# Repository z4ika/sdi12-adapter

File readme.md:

## SDI-12 to USB Type-B Adapter Board PCB
KiCAD project for an adapter powered by a common STM32G431 series microcontroller chip using the on-chip USB capabilities to communicate with a PC relying on VCOM CDC option, to allow for an easy communication.

Current revision includes bidirectional 5V - 3.3V level shifting without logical voltage level inversion. This ensures compability of SDI standard with TTL logic. All of the parts have been standarized and designated manufacturer is JLCPCB. Project includes index.html as BOM listing. 

## 3D renders

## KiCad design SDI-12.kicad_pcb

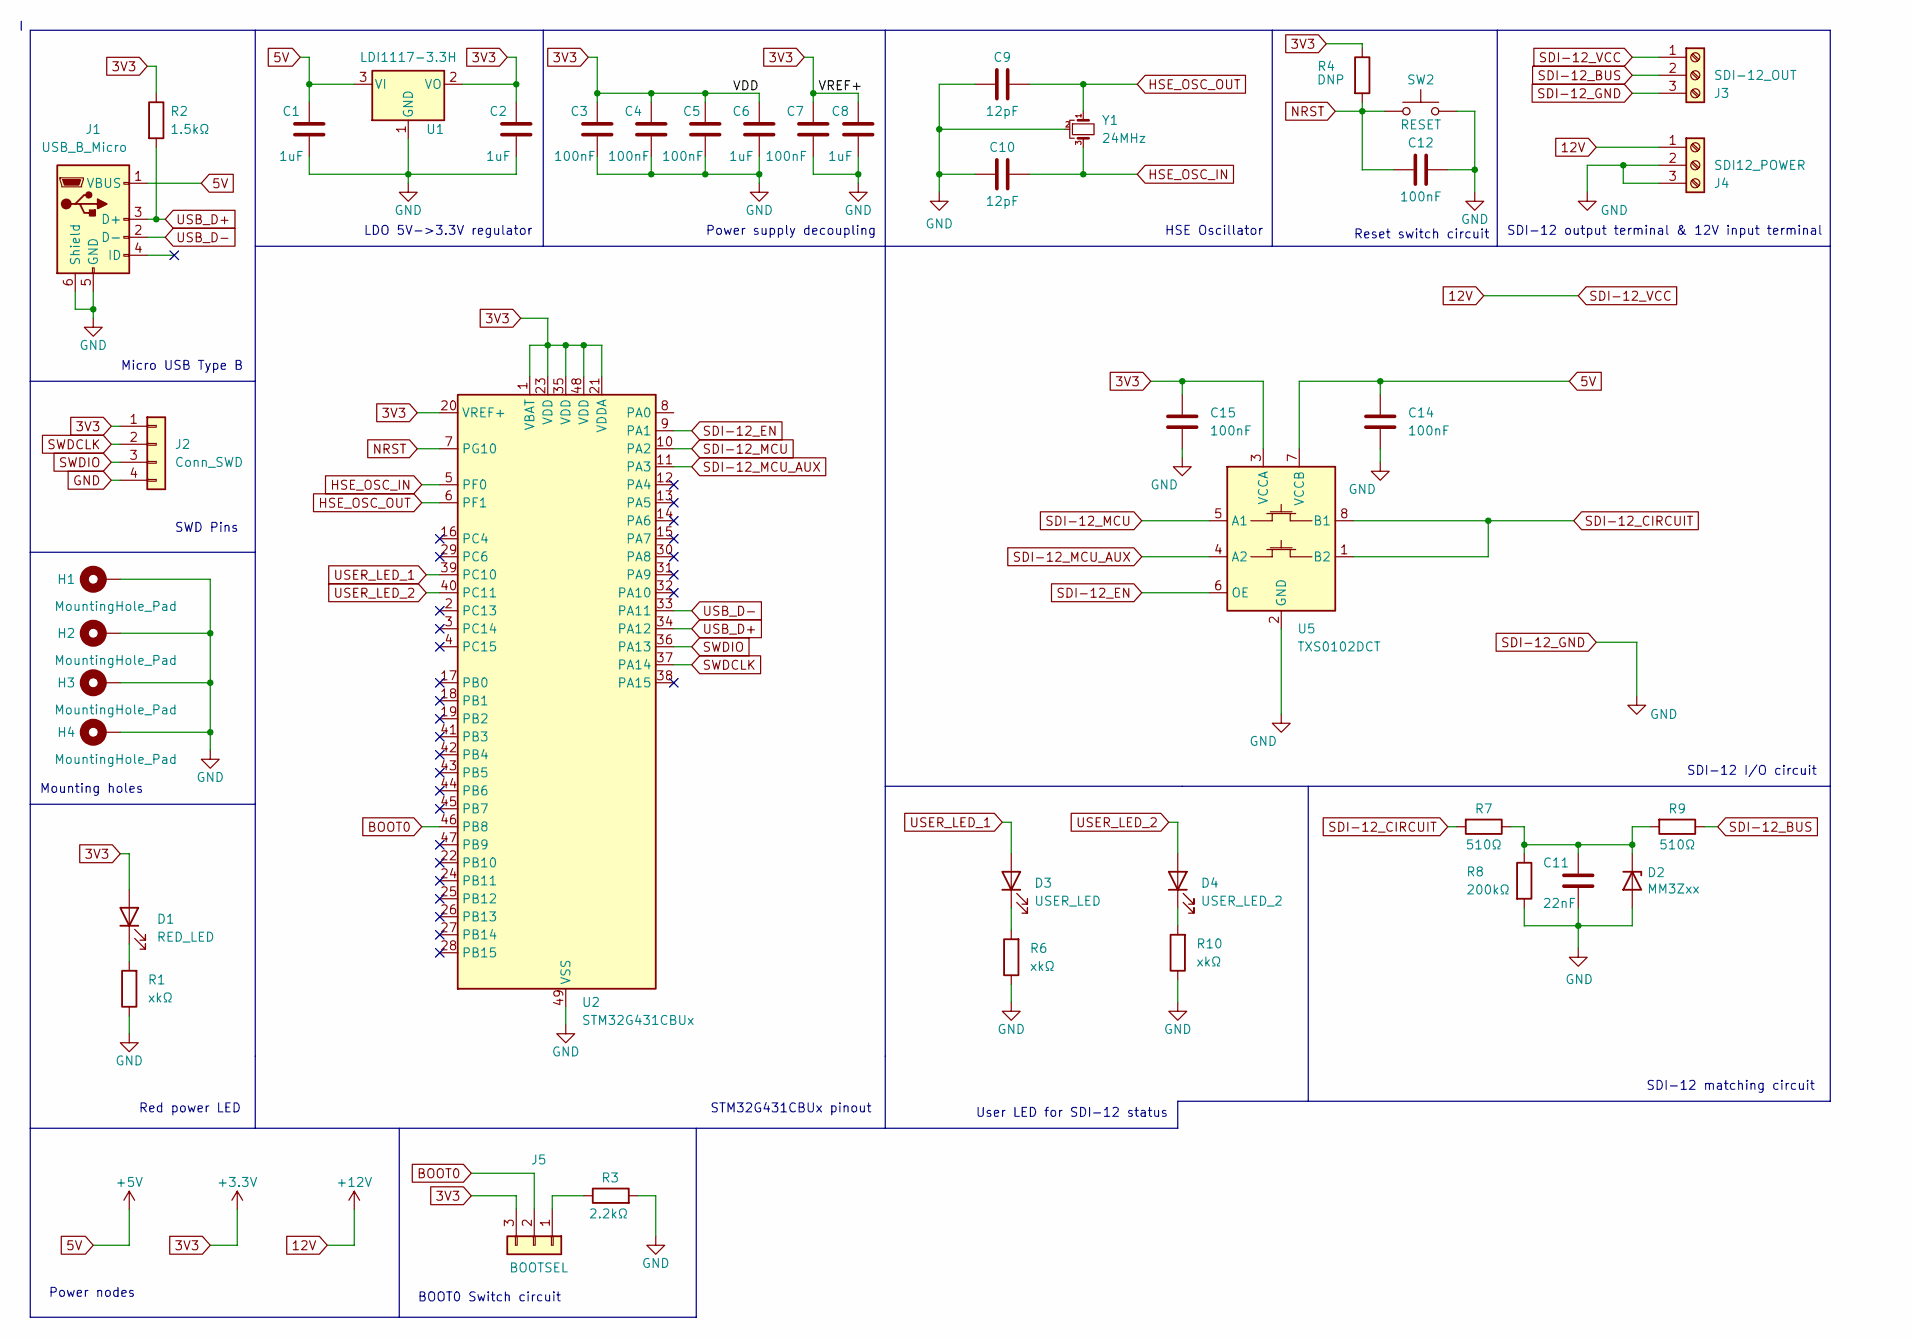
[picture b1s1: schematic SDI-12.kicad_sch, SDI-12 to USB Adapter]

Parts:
C1, C2, C6, C8: 1uF; C_0805_2012Metric
C3, C4, C5, C7, C12, C14, C15: 100nF; C_0603_1608Metric
C9, C10: 12pF; C_0603_1608Metric
C11: 22nF; C_0603_1608Metric
D1: RED_LED; LED_0805_2012Metric
D2: MM3Zxx; D_SOD-323F
D3: USER_LED; LED_0805_2012Metric
D4: USER_LED_2; LED_0805_2012Metric
H1, H2, H3, H4: MountingHole_Pad; MountingHole_2.7mm_Pad_Via
J1: USB_B_Micro; USB_Micro-B_Molex-105017-0001
J2: Conn_SWD; PinHeader_1x04_P2.54mm_Vertical
J3: SDI-12_OUT; TerminalBlock_Phoenix_MPT-0,5-3-2.54_1x03_P2.54mm_Horizontal
J4: SDI12_POWER; TerminalBlock_Phoenix_MPT-0,5-3-2.54_1x03_P2.54mm_Horizontal
J5: BOOTSEL; PinHeader_1x03_P2.54mm_Vertical
R1, R6, R10: xkΩ; R_0603_1608Metric
R2: 1.5kΩ; R_0603_1608Metric
R3: 2.2kΩ; R_0603_1608Metric
R4: DNP; R_0603_1608Metric
R7, R9: 510Ω; R_0603_1608Metric
R8: 200kΩ; R_0603_1608Metric
SW2: RESET; SW_SPST_B3U-1000P
U1: LDI1117-3.3H; SOT-223-3_TabPin2
U2: STM32G431CBUx; QFN-48-1EP_7x7mm_P0.5mm_EP5.6x5.6mm
U5: TXS0102DCT; SSOP-8_2.95x2.8mm_P0.65mm
Y1: 24MHz; Crystal_SMD_3225-4Pin_3.2x2.5mm

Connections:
3V3: C2.2, C3.2, C4.2, C5.2, C6.2, C7.2, C8.2, C15.1, D1.2 (A), J2.1, J5.3, R2.1, R4.1, U1.2 (VO), U2.1 (VBAT), U2.20 (VREF+), U2.21 (VDDA), U2.23 (VDD), U2.35 (VDD), U2.48 (VDD), U5.3 (VCCA)
5V: C1.2, C14.1, J1.1 (VBUS), U1.3 (VI), U5.7 (VCCB)
12V: J3.1, J4.1
BOOT0: J5.2, U2.46 (PB8)
GND: C1.1, C2.1, C3.1, C4.1, C5.1, C6.1, C7.1, C8.1, C9.1, C10.1, C11.2, C12.2, C14.2, C15.2, D2.2 (A), H1.1, H2.1, H3.1, H4.1, J1.5 (GND), J1.6 (Shield), J2.4, J3.3, J4.2, J4.3, R1.1, R3.2, R6.1, R8.2, R10.1, SW2.2, U1.1 (GND), U2.49 (VSS), U5.2 (GND), Y1.2
HSE_OSC_IN: C10.2, U2.5 (PF0), Y1.3
HSE_OSC_OUT: C9.2, U2.6 (PF1), Y1.1
NRST: C12.1, R4.2, SW2.1, U2.7 (PG10)
unnamed: D1.1 (K), R1.2
unnamed: C11.1, D2.1 (K), R7.1, R8.1, R9.2
unnamed: D3.1 (K), R6.2
unnamed: D4.1 (K), R10.2
unnamed: J5.1, R3.1
SDI-12_BUS: J3.2, R9.1
SDI-12_CIRCUIT: R7.2, U5.1 (B2), U5.8 (B1)
SDI-12_EN: U2.9 (PA1), U5.6 (OE)
SDI-12_MCU: U2.10 (PA2), U5.5 (A1)
SDI-12_MCU_AUX: U2.11 (PA3), U5.4 (A2)
SWDCLK: J2.2, U2.37 (PA14)
SWDIO: J2.3, U2.36 (PA13)
USB_D+: J1.3 (D+), R2.2, U2.34 (PA12)
USB_D-: J1.2 (D-), U2.33 (PA11)
USER_LED_1: D3.2 (A), U2.39 (PC10)
USER_LED_2: D4.2 (A), U2.40 (PC11)

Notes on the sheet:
SWD Pins
Red power LED
LDO 5V->3.3V regulator
Micro USB Type B
SDI-12 I/O circuit
STM32G431CBUx pinout
Reset switch circuit
SDI-12 matching circuit
Power nodes
SDI-12 output terminal & 12V input terminal
User LED for SDI-12 status
HSE Oscillator
Power supply decoupling
Mounting holes
BOOT0 Switch circuit

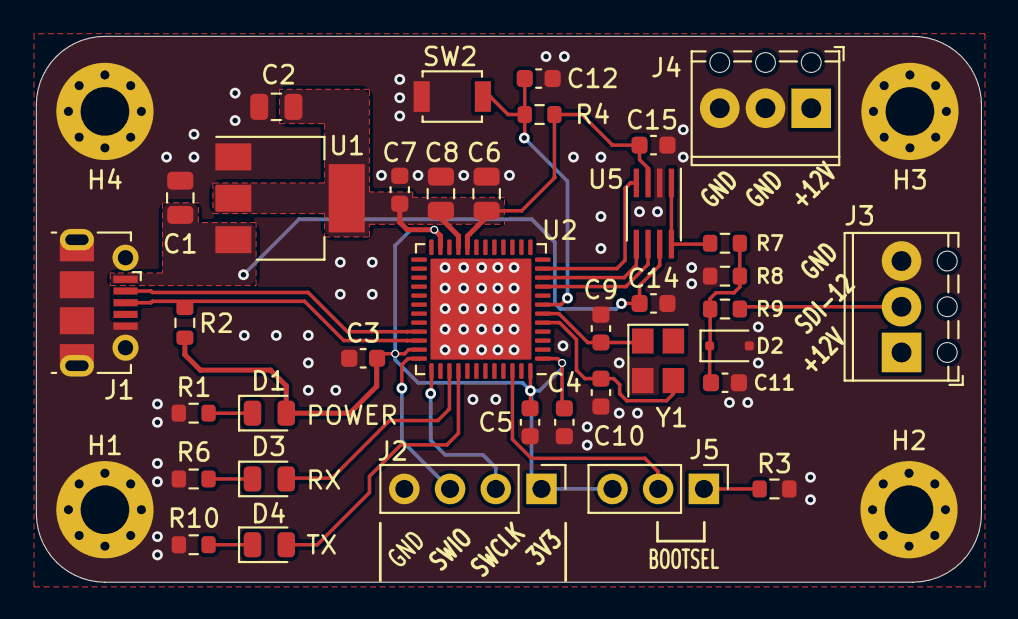
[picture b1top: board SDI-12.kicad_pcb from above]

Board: 4 copper layers, 52.5 x 30.3 mm, 41 parts (0 on the bottom side), 24 nets.

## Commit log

2023-04-17 KiCAD 7.0 project & BOM website
2023-04-24 - Crystal oscillator value changed to proper 16MHz - Minor font changes - Readme document - git lfs for readme graphics
2023-12-14 - STM32F103 replaced with G431 counterpart - TXS0102x for voltage level shifting - Added LED's for I/O status
